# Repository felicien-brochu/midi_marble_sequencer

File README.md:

# MIDI Marble Sequencer

MIDI Marble Sequencer is a hardware + firmware project that detects marbles on IR sensor tracks and outputs MIDI over USB. The system is split into a main ESP-IDF firmware (sequencer + USB MIDI) and ESP32-based control boards (Arduino/PlatformIO) connected over I2C.

## Repository layout

- `hardware/` — CAD (SolidWorks parts/assemblies) and related manufacturing files.
- `software/`
	- `midi_marble_sequencer_main/` — main firmware (ESP-IDF) for the sequencer + USB MIDI.
	- `midi_marble_sequencer_controls_main/` — main control board firmware (PlatformIO/Arduino).
	- `midi_marble_sequencer_controls_pages/` — pages control board firmware (PlatformIO/Arduino).
	- `common_src/` — shared code used by the control board firmwares.
	- `smab_midi_mapper/` — JUCE utility app (see its README).
	- `stats/` — calibration/statistics data exports.

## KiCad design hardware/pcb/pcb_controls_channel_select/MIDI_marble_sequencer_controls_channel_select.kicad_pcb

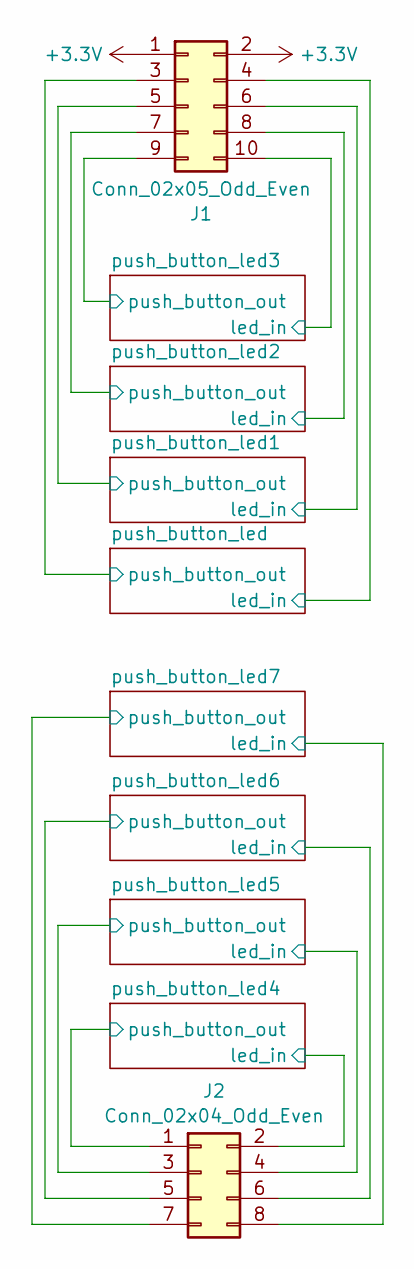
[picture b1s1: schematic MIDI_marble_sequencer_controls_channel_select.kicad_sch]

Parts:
J1: Conn_02x05_Odd_Even; PinHeader_2x05_P2.54mm_Vertical
J2: Conn_02x04_Odd_Even; PinHeader_2x04_P2.54mm_Vertical

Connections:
+3.3V: J1.1, J1.2; also elsewhere on the board
/push_button_led1/led_in: J1.6; also elsewhere on the board
/push_button_led1/push_button_out: J1.5; also elsewhere on the board
/push_button_led2/led_in: J1.8; also elsewhere on the board
/push_button_led2/push_button_out: J1.7; also elsewhere on the board
/push_button_led3/led_in: J1.10; also elsewhere on the board
/push_button_led3/push_button_out: J1.9; also elsewhere on the board
/push_button_led4/led_in: J2.2; also elsewhere on the board
/push_button_led4/push_button_out: J2.1; also elsewhere on the board
/push_button_led5/led_in: J2.4; also elsewhere on the board
/push_button_led5/push_button_out: J2.3; also elsewhere on the board
/push_button_led6/led_in: J2.6; also elsewhere on the board
/push_button_led6/push_button_out: J2.5; also elsewhere on the board
/push_button_led7/led_in: J2.8; also elsewhere on the board
/push_button_led7/push_button_out: J2.7; also elsewhere on the board
/push_button_led/led_in: J1.4; also elsewhere on the board
/push_button_led/push_button_out: J1.3; also elsewhere on the board

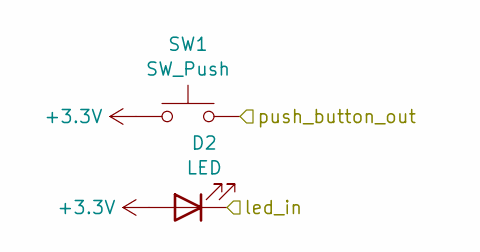
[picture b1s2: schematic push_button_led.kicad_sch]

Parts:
D2: LED; LED_D3.0mm
SW1: SW_Push; SW_Push_1TS009xxxx-xxxx-xxxx_6x6x5mm

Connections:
+3.3V: D2.2 (A), SW1.1; also elsewhere on the board
/push_button_led1/led_in: D2.1 (K); also elsewhere on the board
/push_button_led/push_button_out: SW1.2; also elsewhere on the board

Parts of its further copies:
D1, D3, D4, D5, D6, D7, D8: LED; LED_D3.0mm
SW2, SW3, SW4, SW5, SW6, SW7, SW8: SW_Push; SW_Push_1TS009xxxx-xxxx-xxxx_6x6x5mm

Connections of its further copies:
+3.3V: D1.2 (A), D3.2 (A), D4.2 (A), D5.2 (A), D6.2 (A), D7.2 (A), D8.2 (A), SW2.1, SW3.1, SW4.1, SW5.1, SW6.1, SW7.1, SW8.1; also elsewhere on the board
/push_button_led1/push_button_out: SW2.2; also elsewhere on the board
/push_button_led2/led_in: D3.1 (K); also elsewhere on the board
/push_button_led2/push_button_out: SW3.2; also elsewhere on the board
/push_button_led3/led_in: D4.1 (K); also elsewhere on the board
/push_button_led3/push_button_out: SW4.2; also elsewhere on the board
/push_button_led4/led_in: D5.1 (K); also elsewhere on the board
/push_button_led4/push_button_out: SW5.2; also elsewhere on the board
/push_button_led5/led_in: D6.1 (K); also elsewhere on the board
/push_button_led5/push_button_out: SW6.2; also elsewhere on the board
/push_button_led6/led_in: D7.1 (K); also elsewhere on the board
/push_button_led6/push_button_out: SW7.2; also elsewhere on the board
/push_button_led7/led_in: D8.1 (K); also elsewhere on the board
/push_button_led7/push_button_out: SW8.2; also elsewhere on the board
/push_button_led/led_in: D1.1 (K); also elsewhere on the board

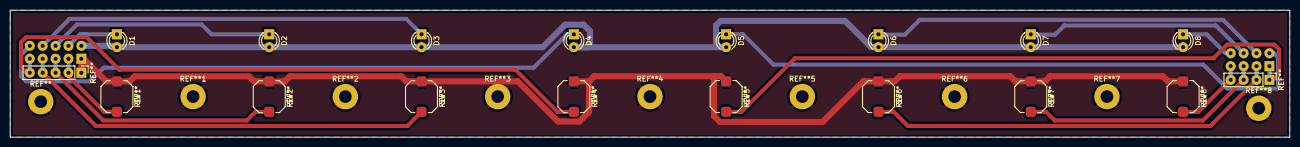
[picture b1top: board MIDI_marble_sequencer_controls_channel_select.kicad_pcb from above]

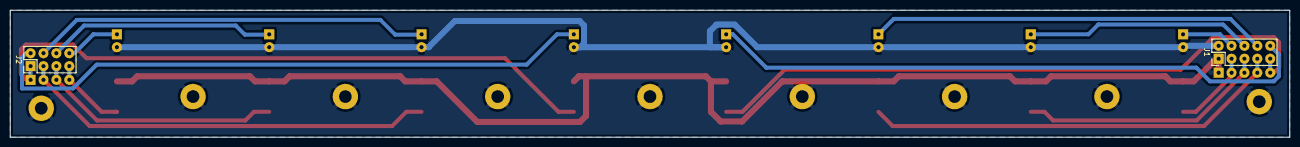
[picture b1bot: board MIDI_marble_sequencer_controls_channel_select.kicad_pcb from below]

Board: 2 copper layers, 252.0 x 25.0 mm, 18 parts (2 on the bottom side), 17 nets.

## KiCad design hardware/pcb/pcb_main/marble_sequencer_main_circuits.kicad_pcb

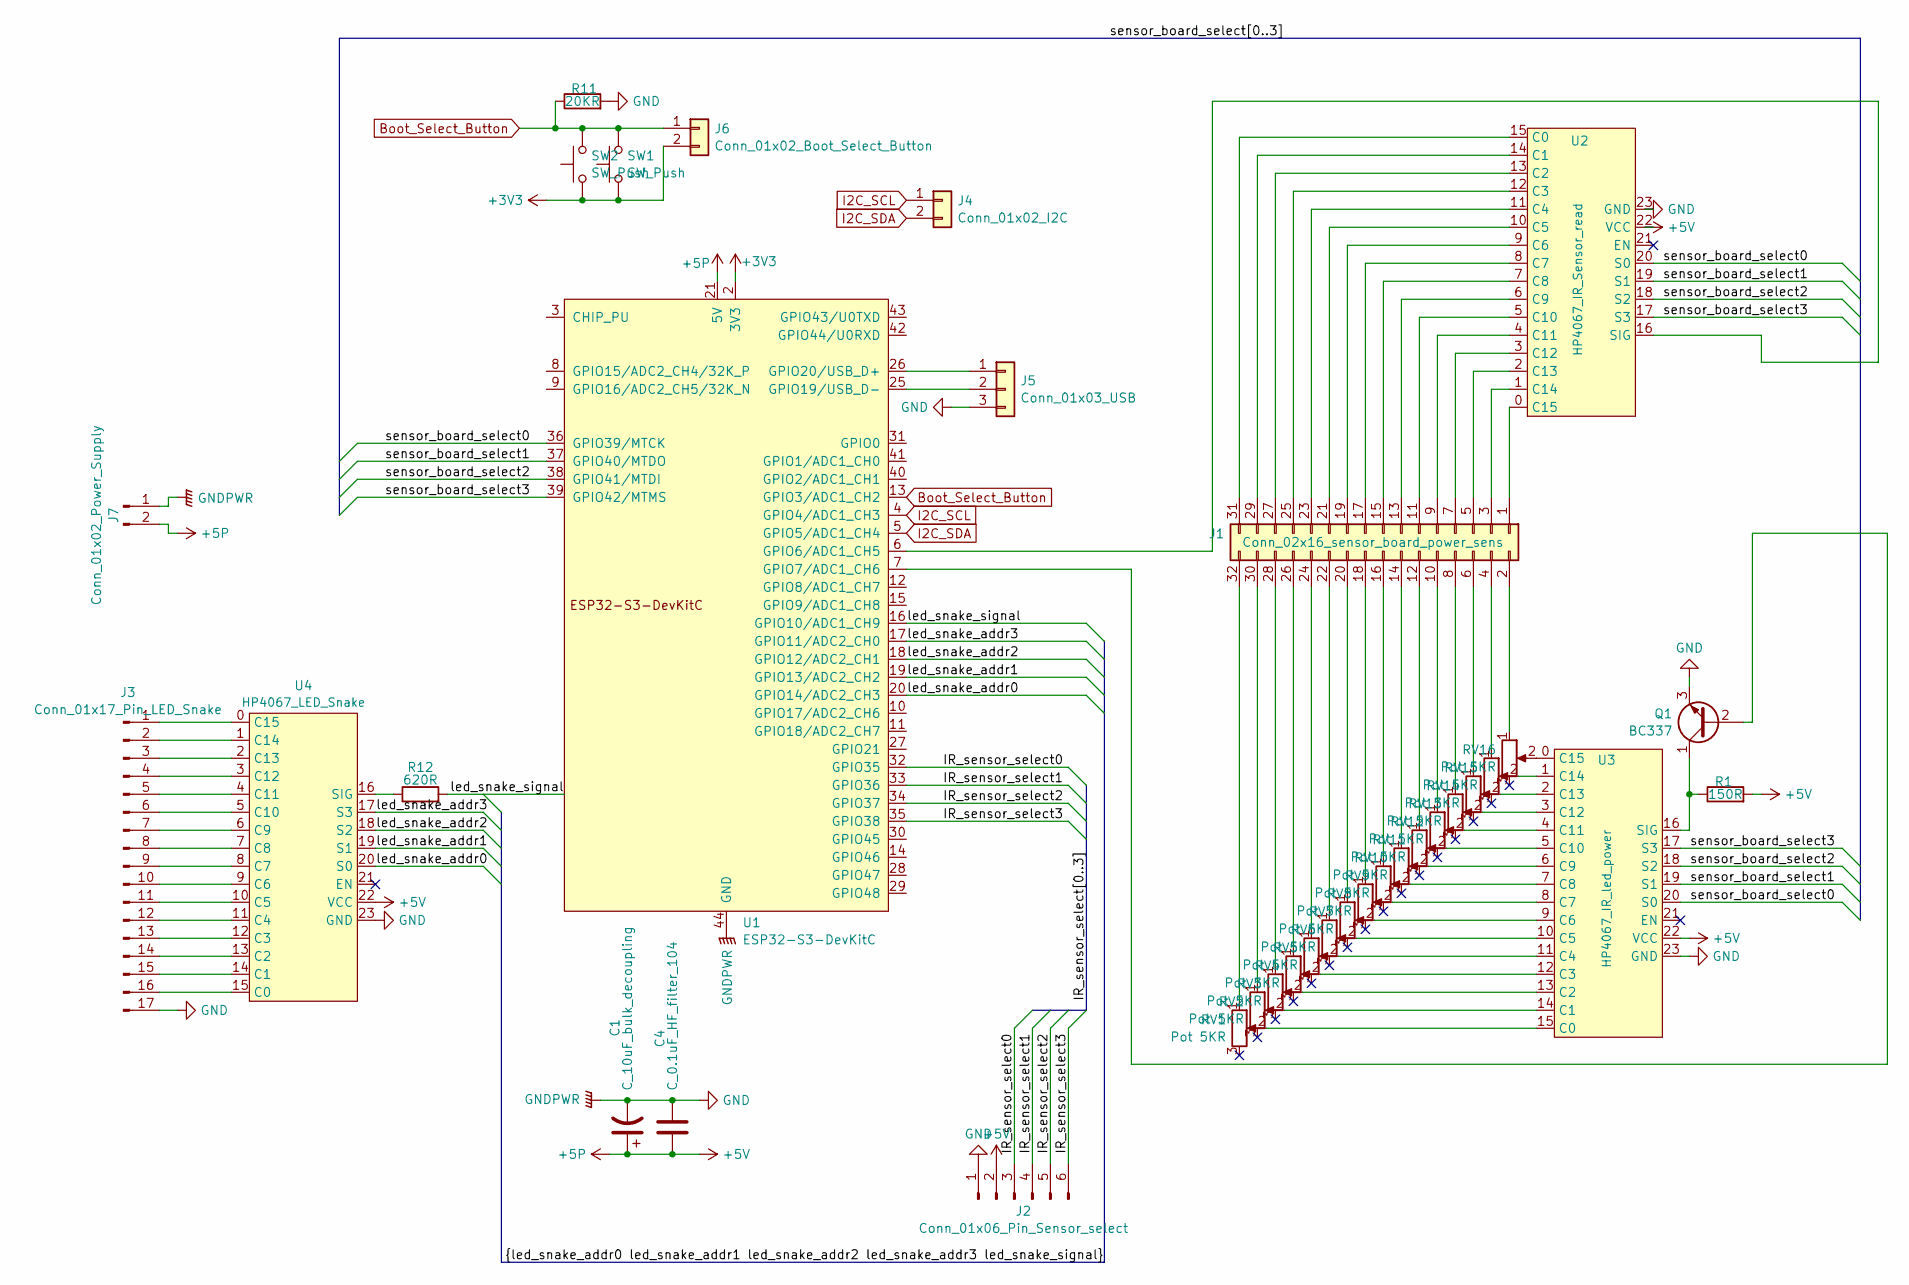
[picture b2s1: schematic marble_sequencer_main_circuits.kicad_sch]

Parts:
C1: C_10uF_bulk_decoupling; CP_Radial_D8.0mm_P5.00mm
C4: C_0.1uF_HF_filter_104; C_Disc_D5.0mm_W2.5mm_P5.00mm
J1: Conn_02x16_sensor_board_power_sens; PinHeader_2x16_P2.54mm_Vertical
J2: Conn_01x06_Pin_Sensor_select; PhoenixContact_MSTBVA_2,5_6-G-5,08_1x06_P5.08mm_Vertical
J3: Conn_01x17_Pin_LED_Snake; PinHeader_1x17_P2.54mm_Vertical
J4: Conn_01x02_I2C; PhoenixContact_MSTBVA_2,5_2-G-5,08_1x02_P5.08mm_Vertical
J5: Conn_01x03_USB; PhoenixContact_MSTBVA_2,5_3-G-5,08_1x03_P5.08mm_Vertical
J6: Conn_01x02_Boot_Select_Button; PhoenixContact_MSTBVA_2,5_2-G-5,08_1x02_P5.08mm_Vertical
J7: Conn_01x02_Power_Supply; PhoenixContact_MSTBVA_2,5_2-G-5,08_1x02_P5.08mm_Vertical
Q1: BC337; TO-92_Wide
R1: 150R; R_Axial_DIN0617_L17.0mm_D6.0mm_P20.32mm_Horizontal
R11: 20KR; R_Axial_DIN0207_L6.3mm_D2.5mm_P10.16mm_Horizontal_BIG_PADS
R12: 620R; R_Axial_DIN0207_L6.3mm_D2.5mm_P10.16mm_Horizontal_BIG_PADS
RV1, RV2, RV3, RV4, RV5, RV6, RV7, RV8, RV9, RV10, RV11, RV12, RV13, RV14, RV15, RV16: Pot 5KR; Potentiometer_Piher_PT-6-H_Horizontal_Large_Pads
SW1, SW2: SW_Push; SW_Push_1TS009xxxx-xxxx-xxxx_6x6x5mm
U1: ESP32-S3-DevKitC
U2: HP4067_IR_Sensor_read; HP4067_16_ch_analog_mutiplexer_devboard
U3: HP4067_IR_led_power; HP4067_16_ch_analog_mutiplexer_devboard
U4: HP4067_LED_Snake; HP4067_16_ch_analog_mutiplexer_devboard

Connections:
+3V3: J6.2, SW1.1, SW2.1, U1.1 (3V3), U1.2 (3V3)
+5P: C1.1, C4.2, J2.2, J7.2, R1.2, U1.21 (5V), U2.22 (VCC), U3.22 (VCC), U4.22 (VCC)
/IR_sensor_select0: J2.3, U1.32 (GPIO35)
/IR_sensor_select1: J2.4, U1.33 (GPIO36)
/IR_sensor_select2: J2.5, U1.34 (GPIO37)
/IR_sensor_select3: J2.6, U1.35 (GPIO38)
/led_snake_addr0: U1.20 (GPIO14/ADC2_CH3), U4.20 (S0)
/led_snake_addr1: U1.19 (GPIO13/ADC2_CH2), U4.19 (S1)
/led_snake_addr2: U1.18 (GPIO12/ADC2_CH1), U4.18 (S2)
/led_snake_addr3: U1.17 (GPIO11/ADC2_CH0), U4.17 (S3)
/led_snake_signal: R12.2, U1.16 (GPIO10/ADC1_CH9)
/sensor_board_select0: U1.36 (GPIO39/MTCK), U2.20 (S0), U3.20 (S0)
/sensor_board_select1: U1.37 (GPIO40/MTDO), U2.19 (S1), U3.19 (S1)
/sensor_board_select2: U1.38 (GPIO41/MTDI), U2.18 (S2), U3.18 (S2)
/sensor_board_select3: U1.39 (GPIO42/MTMS), U2.17 (S3), U3.17 (S3)
Boot_Select_Button: J6.1, R11.1, SW1.2, SW2.2, U1.13 (GPIO3/ADC1_CH2)
GND: C1.2, C4.1, J2.1, J3.17, J5.3, J7.1, Q1.3 (E), R11.2, U1.22 (GND), U1.23 (GND), U1.24 (GND), U1.44 (GND), U2.23 (GND), U3.23 (GND), U4.23 (GND)
I2C_SCL: J4.1, U1.4 (GPIO4/ADC1_CH3)
I2C_SDA: J4.2, U1.5 (GPIO5/ADC1_CH4)
unnamed: J1.1, U2.0 (C15)
unnamed: J1.2, RV16.1
unnamed: J1.3, U2.1 (C14)
unnamed: J1.4, RV15.1
unnamed: J1.5, U2.2 (C13)
unnamed: J1.6, RV14.1
unnamed: J1.7, U2.3 (C12)
unnamed: J1.8, RV13.1
unnamed: J1.9, U2.4 (C11)
unnamed: J1.10, RV12.1
unnamed: J1.11, U2.5 (C10)
unnamed: J1.12, RV11.1
unnamed: J1.13, U2.6 (C9)
unnamed: J1.14, RV10.1
unnamed: J1.15, U2.7 (C8)
unnamed: J1.16, RV9.1
unnamed: J1.17, U2.8 (C7)
unnamed: J1.18, RV8.1
unnamed: J1.19, U2.9 (C6)
unnamed: J1.20, RV7.1
unnamed: J1.21, U2.10 (C5)
unnamed: J1.22, RV6.1
unnamed: J1.23, U2.11 (C4)
unnamed: J1.24, RV5.1
unnamed: J1.25, U2.12 (C3)
unnamed: J1.26, RV4.1
unnamed: J1.27, U2.13 (C2)
unnamed: J1.28, RV3.1
unnamed: J1.29, U2.14 (C1)
unnamed: J1.30, RV2.1
unnamed: J1.31, U2.15 (C0)
unnamed: J1.32, RV1.1
unnamed: J3.1, U4.0 (C15)
unnamed: J3.2, U4.1 (C14)
unnamed: J3.3, U4.2 (C13)
unnamed: J3.4, U4.3 (C12)
unnamed: J3.5, U4.4 (C11)
unnamed: J3.6, U4.5 (C10)
unnamed: J3.7, U4.6 (C9)
unnamed: J3.8, U4.7 (C8)
unnamed: J3.9, U4.8 (C7)
unnamed: J3.10, U4.9 (C6)
unnamed: J3.11, U4.10 (C5)
unnamed: J3.12, U4.11 (C4)
unnamed: J3.13, U4.12 (C3)
unnamed: J3.14, U4.13 (C2)
unnamed: J3.15, U4.14 (C1)
unnamed: J3.16, U4.15 (C0)
unnamed: J5.1, U1.26 (GPIO20/USB_D+)
unnamed: J5.2, U1.25 (GPIO19/USB_D-)
unnamed: Q1.2 (B), U1.7 (GPIO7/ADC1_CH6)
unnamed: Q1.1 (C), R1.1, U3.16 (SIG)
unnamed: U1.6 (GPIO6/ADC1_CH5), U2.16 (SIG)
unnamed: RV1.2, U3.15 (C0)
unnamed: RV2.2, U3.14 (C1)
unnamed: RV3.2, U3.13 (C2)
unnamed: RV4.2, U3.12 (C3)
unnamed: RV5.2, U3.11 (C4)
unnamed: RV6.2, U3.10 (C5)
unnamed: RV7.2, U3.9 (C6)
unnamed: RV8.2, U3.8 (C7)
unnamed: RV9.2, U3.7 (C8)
unnamed: RV10.2, U3.6 (C9)
unnamed: RV11.2, U3.5 (C10)
unnamed: RV12.2, U3.4 (C11)
unnamed: RV13.2, U3.3 (C12)
unnamed: RV14.2, U3.2 (C13)
unnamed: RV15.2, U3.1 (C14)
unnamed: RV16.2, U3.0 (C15)
unnamed: R12.1, U4.16 (SIG)

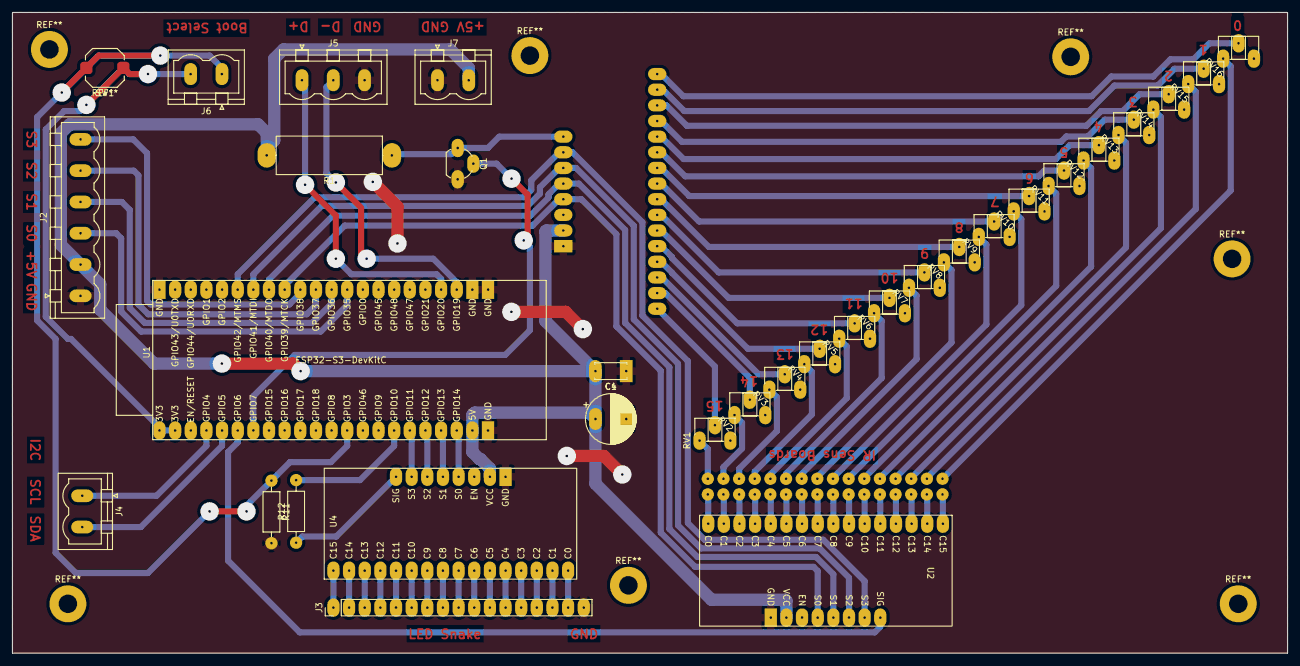
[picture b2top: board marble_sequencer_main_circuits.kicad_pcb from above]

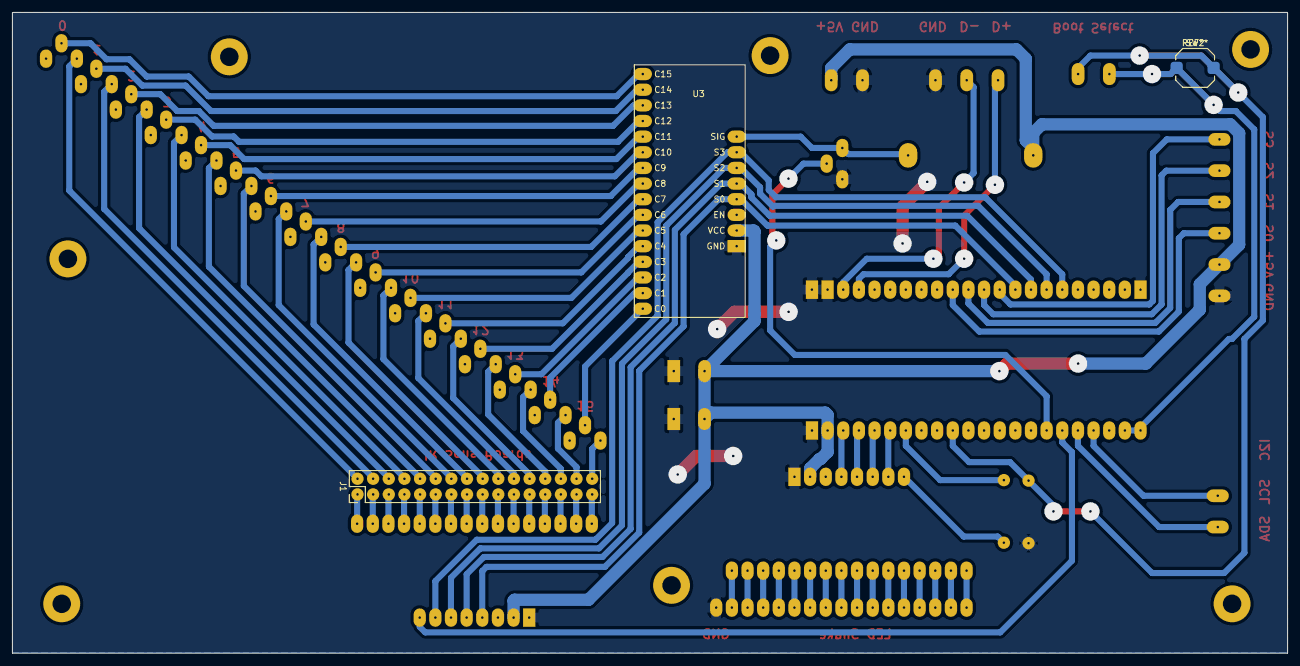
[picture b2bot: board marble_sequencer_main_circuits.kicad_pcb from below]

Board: 2 copper layers, 207.0 x 104.0 mm, 35 parts (3 on the bottom side), 89 nets.

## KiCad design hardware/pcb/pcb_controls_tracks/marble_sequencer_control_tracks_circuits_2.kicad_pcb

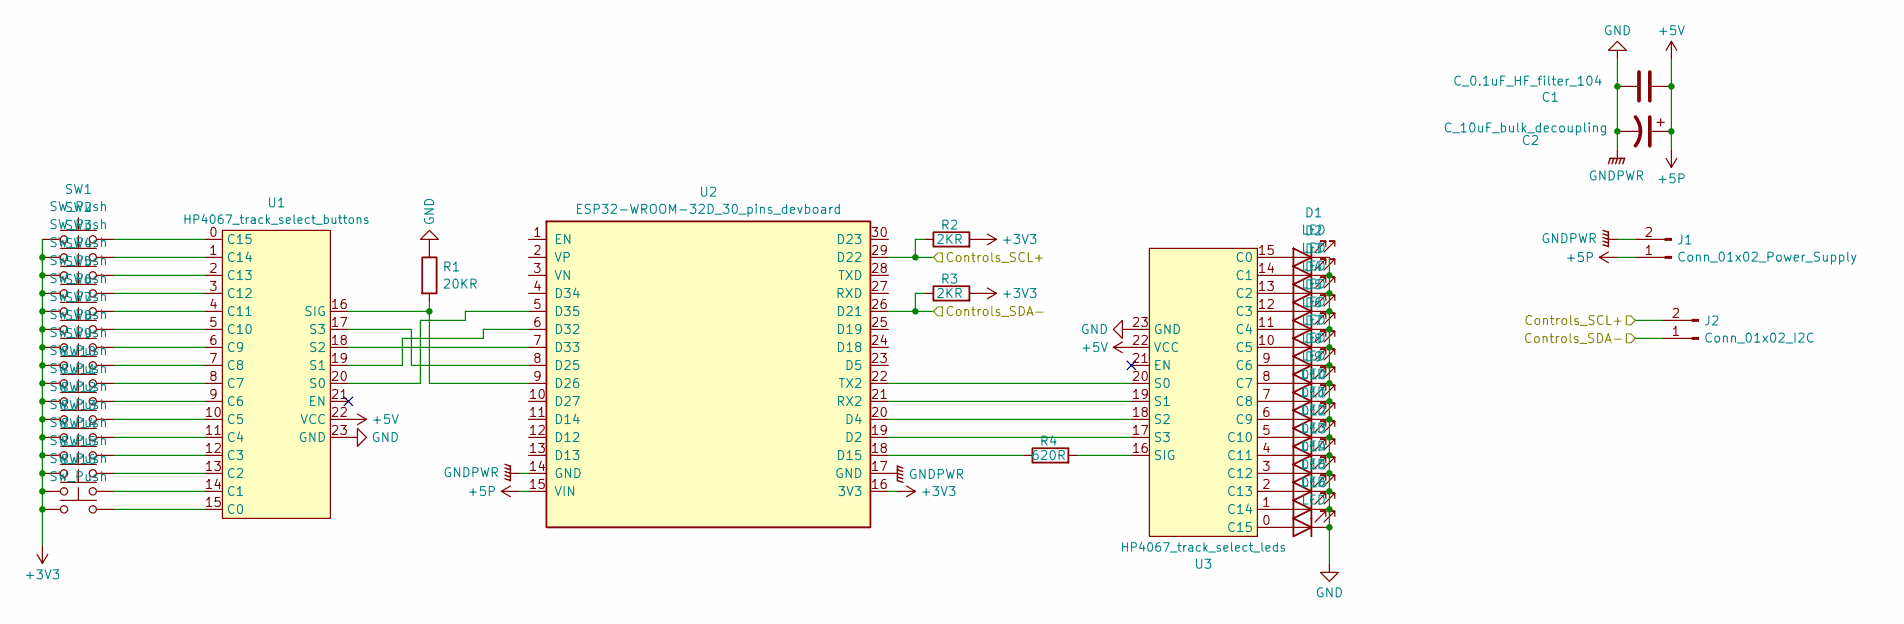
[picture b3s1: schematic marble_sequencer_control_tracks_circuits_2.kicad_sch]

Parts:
C1: C_0.1uF_HF_filter_104; C_Disc_D5.0mm_W2.5mm_P5.00mm
C2: C_10uF_bulk_decoupling; CP_Radial_D8.0mm_P5.00mm
D1, D2, D3, D4, D5, D6, D7, D8, D9, D10, D11, D12, D13, D14, D15, D16: LED; LED_D3.0mm
J1: Conn_01x02_Power_Supply; PhoenixContact_MSTBVA_2,5_2-G-5,08_1x02_P5.08mm_Vertical
J2: Conn_01x02_I2C; PhoenixContact_MSTBVA_2,5_2-G-5,08_1x02_P5.08mm_Vertical
R1: 20KR; R_Axial_DIN0207_L6.3mm_D2.5mm_P10.16mm_Horizontal_BIG_PADS
R2, R3: 2KR; R_Axial_DIN0207_L6.3mm_D2.5mm_P10.16mm_Horizontal_BIG_PADS
R4: 620R; R_Axial_DIN0207_L6.3mm_D2.5mm_P10.16mm_Horizontal_BIG_PADS
SW1, SW2, SW3, SW4, SW5, SW6, SW7, SW8, SW9, SW10, SW11, SW12, SW13, SW14, SW15, SW16: SW_Push; SW_Push_1TS009xxxx-xxxx-xxxx_6x6x5mm
U1: HP4067_track_select_buttons; HP4067_16_ch_analog_mutiplexer_devboard
U2: ESP32-WROOM-32D_30_pins_devboard
U3: HP4067_track_select_leds; HP4067_16_ch_analog_mutiplexer_devboard

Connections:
+3V3: R2.2, R3.2, SW1.1, SW2.1, SW3.1, SW4.1, SW5.1, SW6.1, SW7.1, SW8.1, SW9.1, SW10.1, SW11.1, SW12.1, SW13.1, SW14.1, SW15.1, SW16.1, U2.16 (3V3)
+5P: C1.2, C2.1, J1.1, U1.22 (VCC), U2.15 (VIN), U3.22 (VCC)
/Controls_SCL: J2.2, R2.1, U2.29 (D22)
/Controls_SDA: J2.1, R3.1, U2.26 (D21)
GND: C1.1, C2.2, D1.1 (K), D2.1 (K), D3.1 (K), D4.1 (K), D5.1 (K), D6.1 (K), D7.1 (K), D8.1 (K), D9.1 (K), D10.1 (K), D11.1 (K), D12.1 (K), D13.1 (K), D14.1 (K), D15.1 (K), D16.1 (K), J1.2, R1.1, U1.23 (GND), U2.14 (GND), U2.17 (GND), U3.23 (GND)
unnamed: D1.2 (A), U3.15 (C0)
unnamed: D2.2 (A), U3.14 (C1)
unnamed: D3.2 (A), U3.13 (C2)
unnamed: D4.2 (A), U3.12 (C3)
unnamed: D5.2 (A), U3.11 (C4)
unnamed: D6.2 (A), U3.10 (C5)
unnamed: D7.2 (A), U3.9 (C6)
unnamed: D8.2 (A), U3.8 (C7)
unnamed: D9.2 (A), U3.7 (C8)
unnamed: D10.2 (A), U3.6 (C9)
unnamed: D11.2 (A), U3.5 (C10)
unnamed: D12.2 (A), U3.4 (C11)
unnamed: D13.2 (A), U3.3 (C12)
unnamed: D14.2 (A), U3.2 (C13)
unnamed: D15.2 (A), U3.1 (C14)
unnamed: D16.2 (A), U3.0 (C15)
unnamed: SW16.2, U1.15 (C0)
unnamed: SW15.2, U1.14 (C1)
unnamed: SW14.2, U1.13 (C2)
unnamed: SW13.2, U1.12 (C3)
unnamed: SW12.2, U1.11 (C4)
unnamed: SW11.2, U1.10 (C5)
unnamed: SW10.2, U1.9 (C6)
unnamed: SW9.2, U1.8 (C7)
unnamed: SW8.2, U1.7 (C8)
unnamed: SW7.2, U1.6 (C9)
unnamed: SW6.2, U1.5 (C10)
unnamed: SW5.2, U1.4 (C11)
unnamed: SW4.2, U1.3 (C12)
unnamed: SW3.2, U1.2 (C13)
unnamed: SW2.2, U1.1 (C14)
unnamed: SW1.2, U1.0 (C15)
unnamed: U1.20 (S0), U2.5 (D35)
unnamed: U1.19 (S1), U2.6 (D32)
unnamed: U1.18 (S2), U2.7 (D33)
unnamed: U1.17 (S3), U2.8 (D25)
unnamed: R1.2, U1.16 (SIG), U2.9 (D26)
unnamed: U2.19 (D2), U3.17 (S3)
unnamed: U2.20 (D4), U3.18 (S2)
unnamed: R4.1, U2.18 (D15)
unnamed: U2.21 (RX2), U3.19 (S1)
unnamed: U2.22 (TX2), U3.20 (S0)
unnamed: R4.2, U3.16 (SIG)

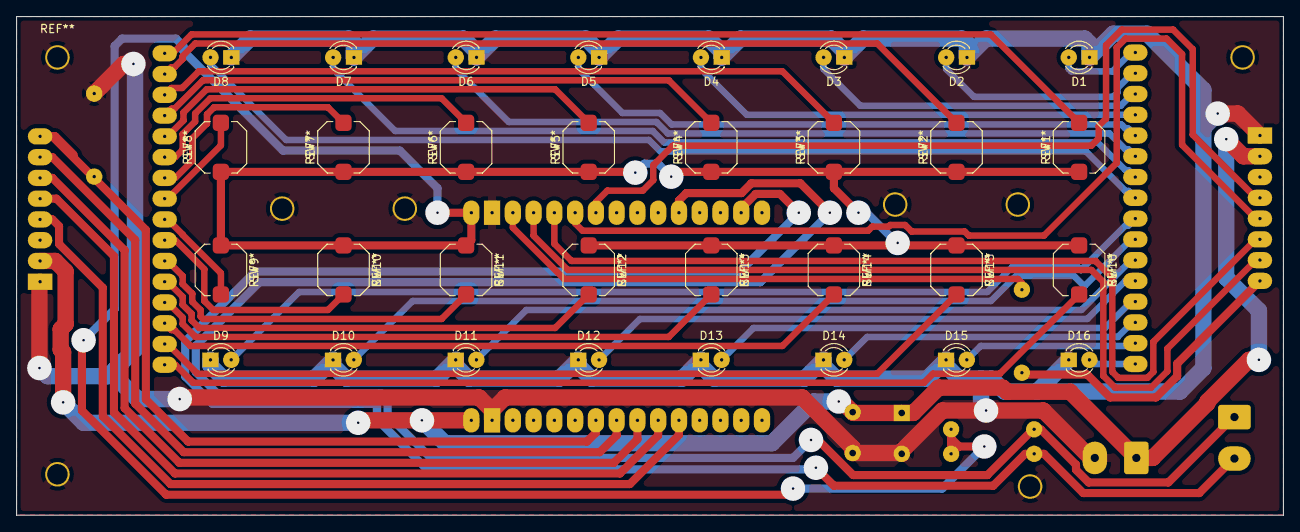
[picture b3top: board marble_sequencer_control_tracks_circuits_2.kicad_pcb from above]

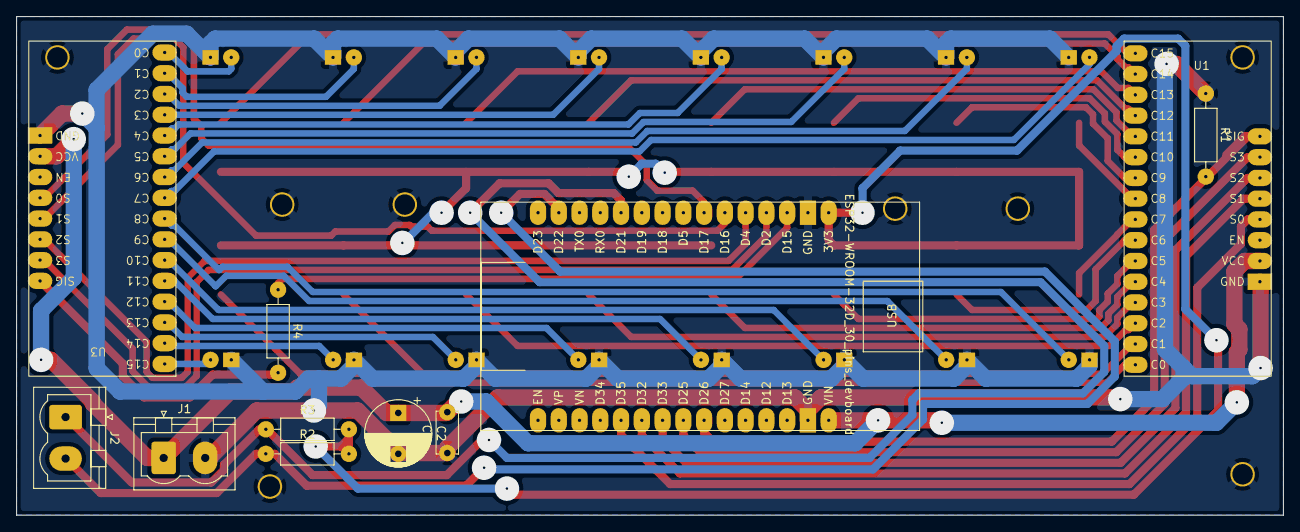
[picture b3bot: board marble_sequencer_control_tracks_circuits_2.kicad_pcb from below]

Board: 2 copper layers, 155.0 x 61.0 mm, 43 parts (11 on the bottom side), 48 nets.

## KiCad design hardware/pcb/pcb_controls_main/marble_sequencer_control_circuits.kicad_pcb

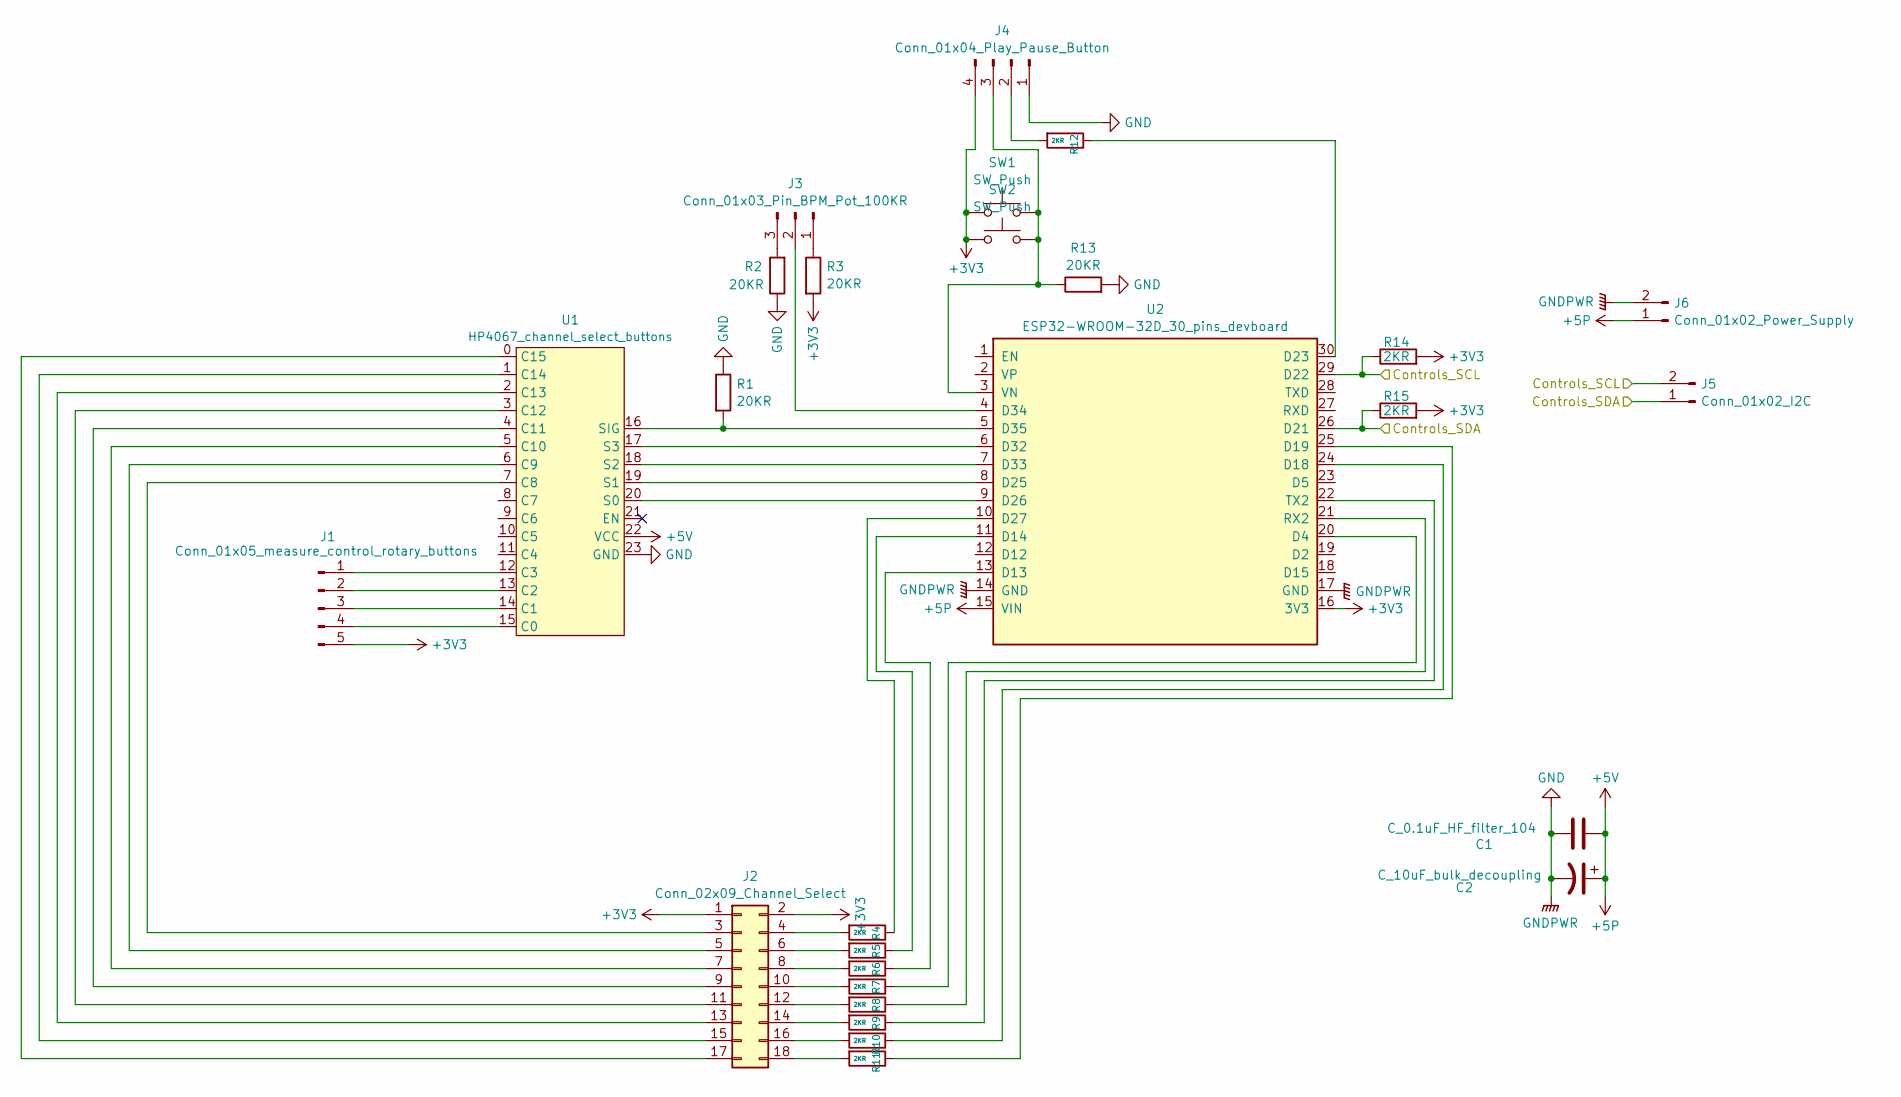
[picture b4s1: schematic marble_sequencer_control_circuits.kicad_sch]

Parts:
C1: C_0.1uF_HF_filter_104; C_Disc_D5.0mm_W2.5mm_P5.00mm
C2: C_10uF_bulk_decoupling; CP_Radial_D8.0mm_P5.00mm
J1: Conn_01x05_measure_control_rotary_buttons; PinHeader_1x05_P2.54mm_Vertical
J2: Conn_02x09_Channel_Select; PinHeader_2x09_P2.54mm_Vertical
J3: Conn_01x03_Pin_BPM_Pot_100KR; PhoenixContact_MSTBVA_2,5_3-G-5,08_1x03_P5.08mm_Vertical
J4: Conn_01x04_Play_Pause_Button; PhoenixContact_MSTBVA_2,5_4-G-5,08_1x04_P5.08mm_Vertical
J5: Conn_01x02_I2C; PhoenixContact_MSTBVA_2,5_2-G-5,08_1x02_P5.08mm_Vertical
J6: Conn_01x02_Power_Supply; PhoenixContact_MSTBVA_2,5_2-G-5,08_1x02_P5.08mm_Vertical
R1, R2, R3, R13: 20KR; R_Axial_DIN0207_L6.3mm_D2.5mm_P10.16mm_Horizontal_BIG_PADS
R4, R5, R6, R7, R8, R9, R10, R11, R12, R14, R15: 2KR; R_Axial_DIN0207_L6.3mm_D2.5mm_P10.16mm_Horizontal_BIG_PADS
SW1, SW2: SW_Push; SW_Push_1TS009xxxx-xxxx-xxxx_6x6x5mm
U1: HP4067_channel_select_buttons; HP4067_16_ch_analog_mutiplexer_devboard
U2: ESP32-WROOM-32D_30_pins_devboard

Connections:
+3V3: J1.5, J2.1, J2.2, J4.4, R3.2, R14.2, R15.2, SW1.1, SW2.1, U2.16 (3V3)
+5P: C1.2, C2.1, J6.1, U1.22 (VCC), U2.15 (VIN)
/Controls_SCL: J5.2, R14.1, U2.29 (D22)
/Controls_SDA: J5.1, R15.1, U2.26 (D21)
GND: C1.1, C2.2, J4.1, J6.2, R1.1, R2.1, R13.2, U1.23 (GND), U2.14 (GND), U2.17 (GND)
unnamed: J1.1, U1.12 (C3)
unnamed: J1.2, U1.13 (C2)
unnamed: J1.3, U1.14 (C1)
unnamed: J1.4, U1.15 (C0)
unnamed: J2.3, U1.7 (C8)
unnamed: J2.4, R4.2
unnamed: J2.5, U1.6 (C9)
unnamed: J2.6, R5.2
unnamed: J2.7, U1.5 (C10)
unnamed: J2.8, R6.2
unnamed: J2.9, U1.4 (C11)
unnamed: J2.10, R7.2
unnamed: J2.11, U1.3 (C12)
unnamed: J2.12, R8.2
unnamed: J2.13, U1.2 (C13)
unnamed: J2.14, R9.2
unnamed: J2.15, U1.1 (C14)
unnamed: J2.16, R10.2
unnamed: J2.17, U1.0 (C15)
unnamed: J2.18, R11.2
unnamed: J3.1, R3.1
unnamed: J3.2, U2.4 (D34)
unnamed: J3.3, R2.2
unnamed: J4.2, R12.2
unnamed: J4.3, R13.1, SW1.2, SW2.2, U2.3 (VN)
unnamed: U1.20 (S0), U2.9 (D26)
unnamed: U1.19 (S1), U2.8 (D25)
unnamed: U1.18 (S2), U2.7 (D33)
unnamed: U1.17 (S3), U2.6 (D32)
unnamed: R1.2, U1.16 (SIG), U2.5 (D35)
unnamed: R7.1, U2.20 (D4)
unnamed: R6.1, U2.13 (D13)
unnamed: R5.1, U2.11 (D14)
unnamed: R10.1, U2.24 (D18)
unnamed: R11.1, U2.25 (D19)
unnamed: R12.1, U2.30 (D23)
unnamed: R4.1, U2.10 (D27)
unnamed: R8.1, U2.21 (RX2)
unnamed: R9.1, U2.22 (TX2)

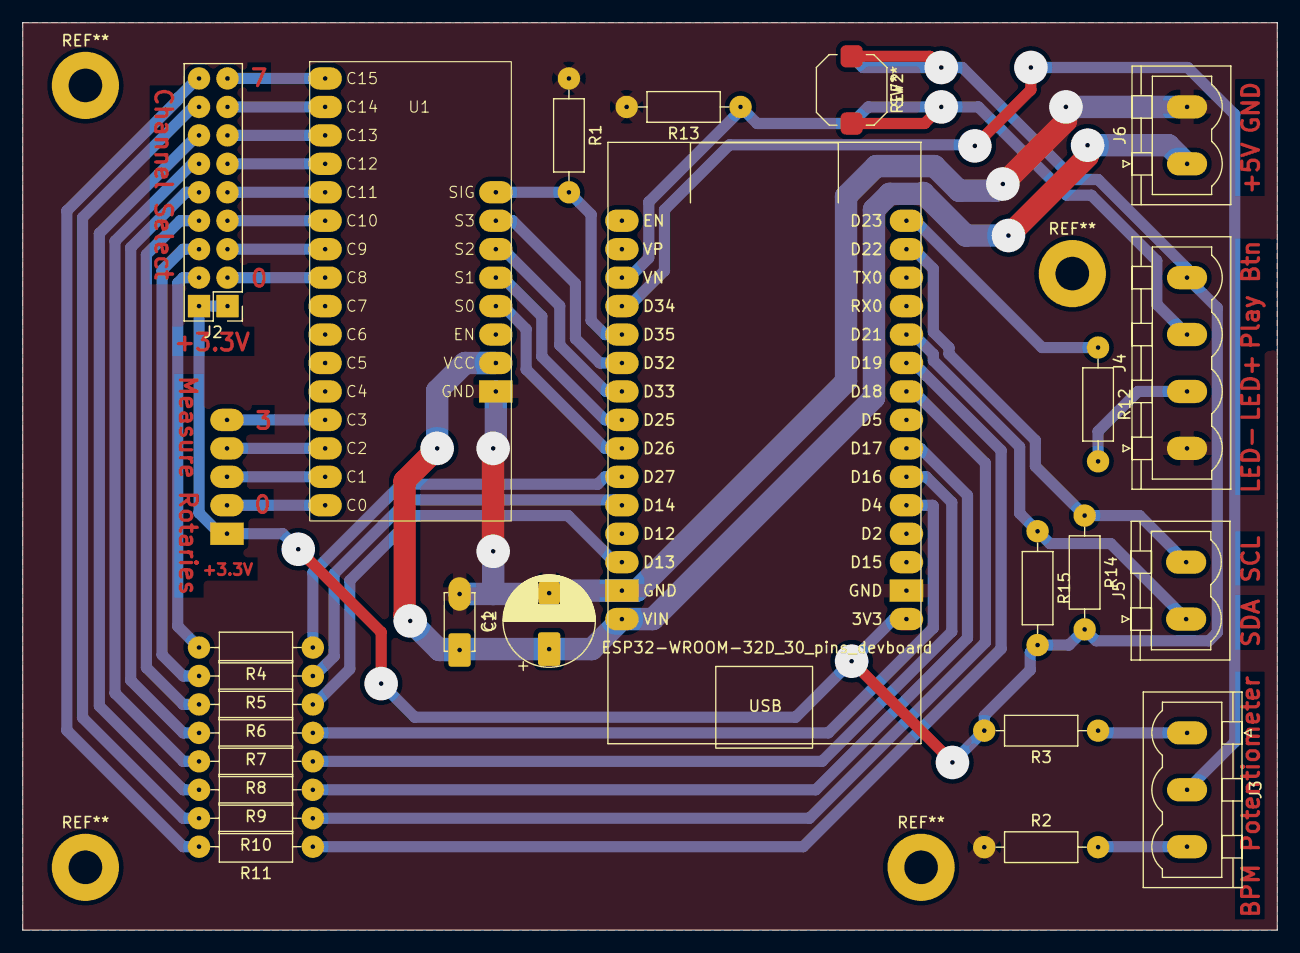
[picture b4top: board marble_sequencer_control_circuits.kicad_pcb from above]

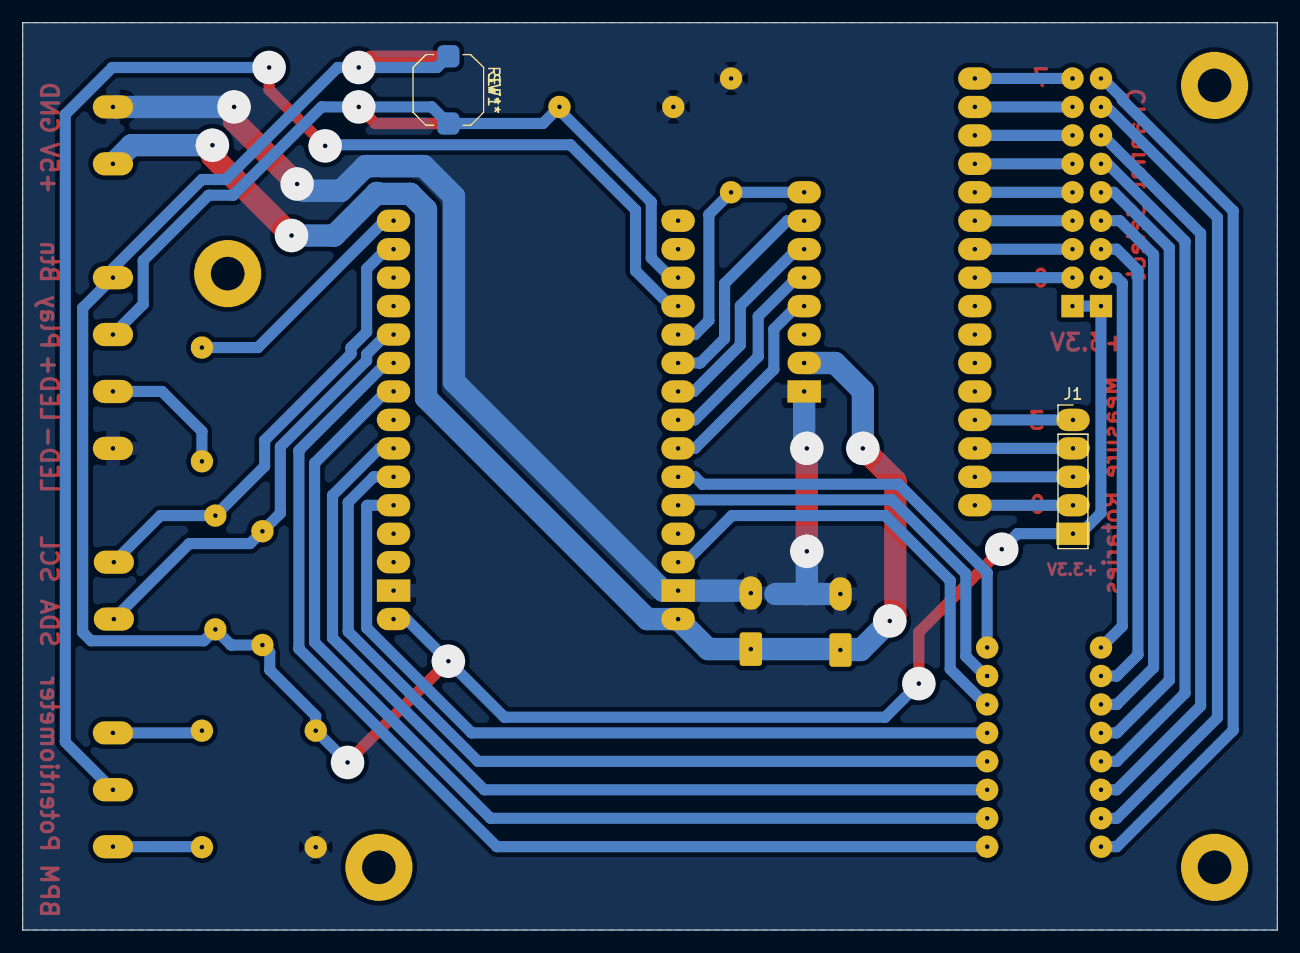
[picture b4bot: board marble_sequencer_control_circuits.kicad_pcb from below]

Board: 2 copper layers, 112.0 x 81.0 mm, 27 parts (2 on the bottom side), 44 nets.
